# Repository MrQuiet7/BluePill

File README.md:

# BluePill
My custom STM32 Blue Pill redesign created in KiCad 9 (40×75 mm, 2-layer PCB) — personal hardware design showcase.

# STM32 Blue Pill Custom Board (KiCad 9)

This is a **custom PCB design** for the STM32F103C8T6 microcontroller (“Blue Pill”) created in **KiCad 9**.

```markdown

## 🧠 Overview
A modern redesign of the classic Blue Pill board, intended for easier prototyping and better reliability.

### ⚙️ Specifications
| Feature | Description |
|----------|--------------|
| **MCU** | STM32F103C8T6 (ARM Cortex-M3) |
| **Board Dimensions** | 40mm × 75mm |
| **USB** | Micro USB port for power and programming |
| **Clock** | 8 MHz main crystal + 32.768 kHz RTC crystal |
| **Programming Header** | SWD (4-pin) |
| **Voltage Regulator** | AMS1117-3.3 or compatible |
| **Power Input** | 5V via USB or pin header |
| **LEDs** | Power and user indicator LEDs |

## 🛠️ Tools Used
- **KiCad 9.0**
- **FreeCAD / Fusion 360** (optional, for 3D model editing)
- **ST-Link V2** for programming and debugging

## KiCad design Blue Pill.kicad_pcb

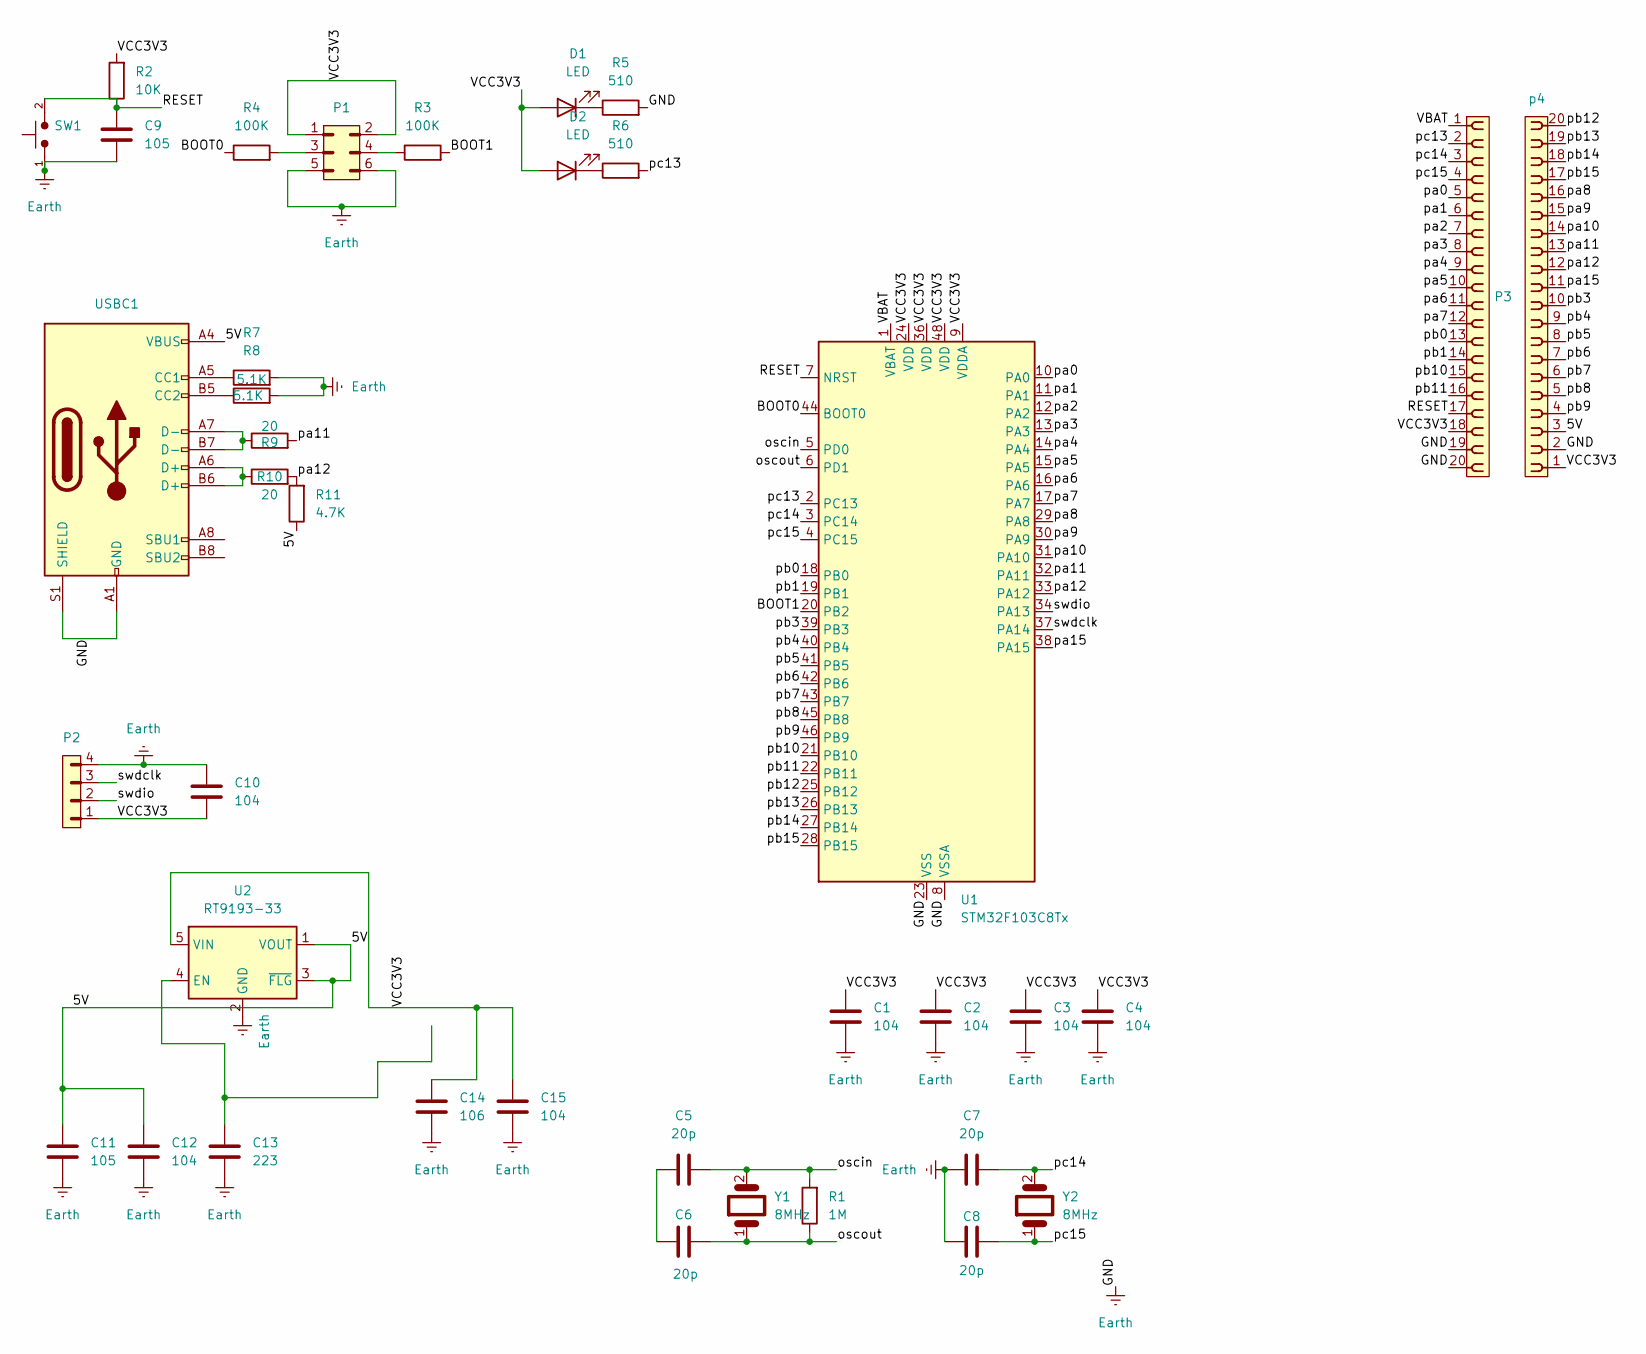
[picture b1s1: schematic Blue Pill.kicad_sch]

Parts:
C1, C2, C3, C4, C10, C12, C15: 104; C_0805_2012Metric_Pad1.18x1.45mm_HandSolder
C5, C6, C7, C8: 20p; C_0805_2012Metric_Pad1.18x1.45mm_HandSolder
C9, C11: 105; C_0805_2012Metric_Pad1.18x1.45mm_HandSolder
C13: 223; C_0805_2012Metric_Pad1.18x1.45mm_HandSolder
C14: 106; C_0805_2012Metric_Pad1.18x1.45mm_HandSolder
D1, D2: LED; LED_1206_3216Metric_Pad1.42x1.75mm_HandSolder
P1: PINHD_2x3_Male; PinHeader_2x03_P2.54mm_Vertical
P2: PINHD_1x4_Male; PinHeader_1x04_P2.54mm_Vertical
P3: PINHD_1x20_Female; PinSocket_1x20_P2.54mm_Vertical
R1: 1M; R_0603_1608Metric_Pad1.05x0.95mm_HandSolder
R2: 10K; R_0603_1608Metric_Pad1.05x0.95mm_HandSolder
R3, R4: 100K; R_0603_1608Metric_Pad1.05x0.95mm_HandSolder
R5, R6: 510; R_0603_1608Metric_Pad1.05x0.95mm_HandSolder
R7, R8: 5.1K; R_0603_1608Metric_Pad1.05x0.95mm_HandSolder
R9, R10: 20; R_0603_1608Metric_Pad1.05x0.95mm_HandSolder
R11: 4.7K; R_0603_1608Metric_Pad1.05x0.95mm_HandSolder
SW1: Push_Button; SW_PUSH_6mm
U1: STM32F103C8Tx; LQFP-48_7x7mm_P0.5mm
U2: RT9193-33; TSOT-23-5
USBC1: USB_C_Receptacle_USB2.0_16P; USB_C_Receptacle_G-Switch_GT-USB-7010ASV
Y1, Y2: 8MHz; Crystal_HC49-4H_Vertical
p4: PINHD_1x20_Female; PinSocket_1x20_P2.54mm_Vertical

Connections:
/5V: C11.2, C12.2, R11.1, U2.1 (VOUT), U2.3 (~FLG), USBC1.A4 (VBUS), USBC1.A9 (VBUS), USBC1.B4 (VBUS), USBC1.B9 (VBUS), p4.3
/BOOT0: R4.1, U1.44 (BOOT0)
/BOOT1: R3.2, U1.20 (PB2)
/RESET: C9.1, P3.17, R2.1, SW1.2, U1.7 (NRST)
/VBAT: P3.1, U1.1 (VBAT)
/VCC3V3: C1.1, C2.1, C3.1, C4.1, C10.1, C14.2, C15.2, D1.2 (A), D2.2 (A), P1.1, P1.2, P2.1, P3.18, R2.2, U1.9 (VDDA), U1.24 (VDD), U1.36 (VDD), U1.48 (VDD), U2.5 (VIN), p4.1
/oscin: C5.2, R1.2, U1.5 (PD0), Y1.2
/oscout: C6.2, R1.1, U1.6 (PD1), Y1.1
/pa0: P3.5, U1.10 (PA0)
/pa1: P3.6, U1.11 (PA1)
/pa2: P3.7, U1.12 (PA2)
/pa3: P3.8, U1.13 (PA3)
/pa4: P3.9, U1.14 (PA4)
/pa5: P3.10, U1.15 (PA5)
/pa6: P3.11, U1.16 (PA6)
/pa7: P3.12, U1.17 (PA7)
/pa8: U1.29 (PA8), p4.16
/pa9: U1.30 (PA9), p4.15
/pa10: U1.31 (PA10), p4.14
/pa11: R9.2, U1.32 (PA11), p4.13
/pa12: R10.2, R11.2, U1.33 (PA12), p4.12
/pa15: U1.38 (PA15), p4.11
/pb0: P3.13, U1.18 (PB0)
/pb1: P3.14, U1.19 (PB1)
/pb3: U1.39 (PB3), p4.10
/pb4: U1.40 (PB4), p4.9
/pb5: U1.41 (PB5), p4.8
/pb6: U1.42 (PB6), p4.7
/pb7: U1.43 (PB7), p4.6
/pb8: U1.45 (PB8), p4.5
/pb9: U1.46 (PB9), p4.4
/pb10: P3.15, U1.21 (PB10)
/pb11: P3.16, U1.22 (PB11)
/pb12: U1.25 (PB12), p4.20
/pb13: U1.26 (PB13), p4.19
/pb14: U1.27 (PB14), p4.18
/pb15: U1.28 (PB15), p4.17
/pc13: P3.2, R6.2, U1.2 (PC13)
/pc14: C7.2, P3.3, U1.3 (PC14), Y2.2
/pc15: C8.2, P3.4, U1.4 (PC15), Y2.1
/swdclk: P2.3, U1.37 (PA14)
/swdio: P2.2, U1.34 (PA13)
Earth: C1.2, C2.2, C3.2, C4.2, C7.1, C8.1, C9.2, C10.2, C11.1, C12.1, C13.1, C14.1, C15.1, P1.5, P1.6, P2.4, P3.19, P3.20, R5.2, R7.2, R8.2, SW1.1, U1.8 (VSSA), U1.23 (VSS), U1.35 (VSS), U1.47 (VSS), U2.2 (GND), USBC1.A1 (GND), USBC1.A12 (GND), USBC1.B1 (GND), USBC1.B12 (GND), USBC1.S1 (SHIELD), p4.2
unnamed: C5.1, C6.1
unnamed: D1.1 (K), R5.1
unnamed: D2.1 (K), R6.1
unnamed: P1.3, R4.2
unnamed: P1.4, R3.1
unnamed: R9.1, USBC1.A7 (D-), USBC1.B7 (D-)
unnamed: R10.1, USBC1.A6 (D+), USBC1.B6 (D+)
unnamed: C13.2, U2.4 (EN)
unnamed: R7.1, USBC1.A5 (CC1)
unnamed: R8.1, USBC1.B5 (CC2)

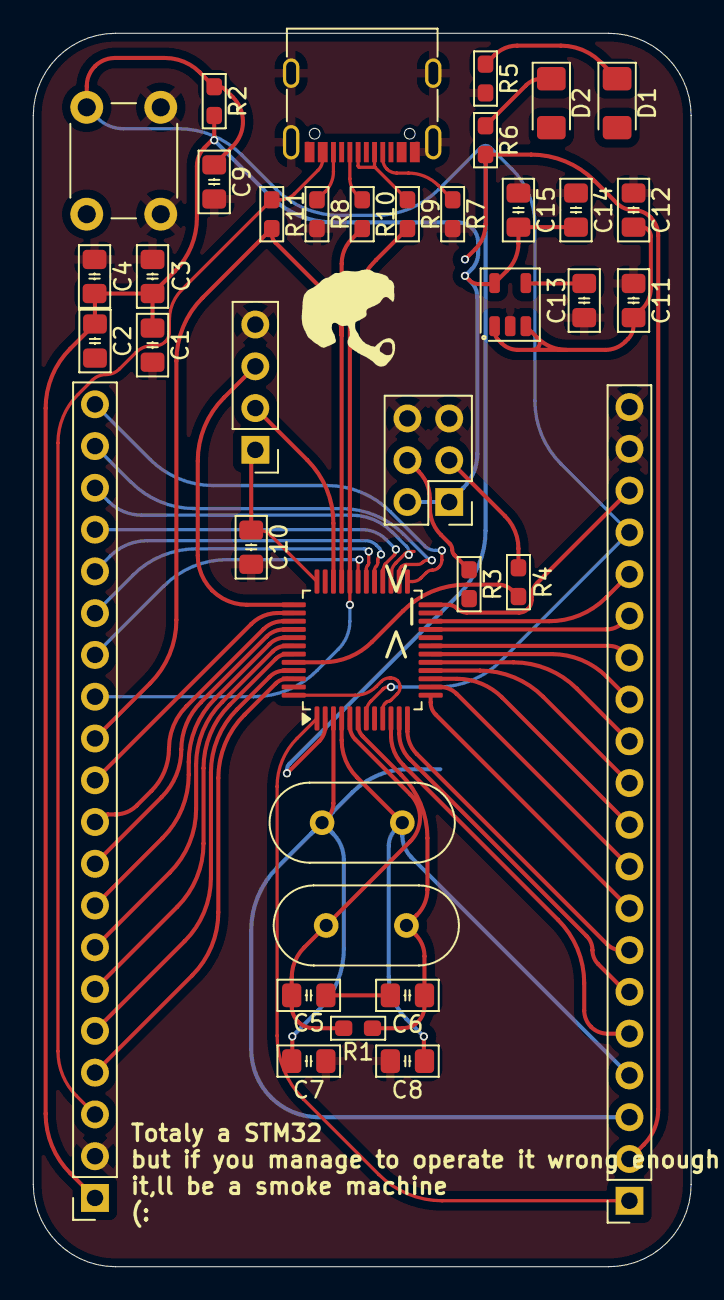
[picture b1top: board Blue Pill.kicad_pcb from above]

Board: 2 copper layers, 40.0 x 75.0 mm, 38 parts (0 on the bottom side), 53 nets.

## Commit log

2025-10-23 Rename original-schematic-STM32F103C8T6-Blue_Pill.pdf to schematic.pdf
